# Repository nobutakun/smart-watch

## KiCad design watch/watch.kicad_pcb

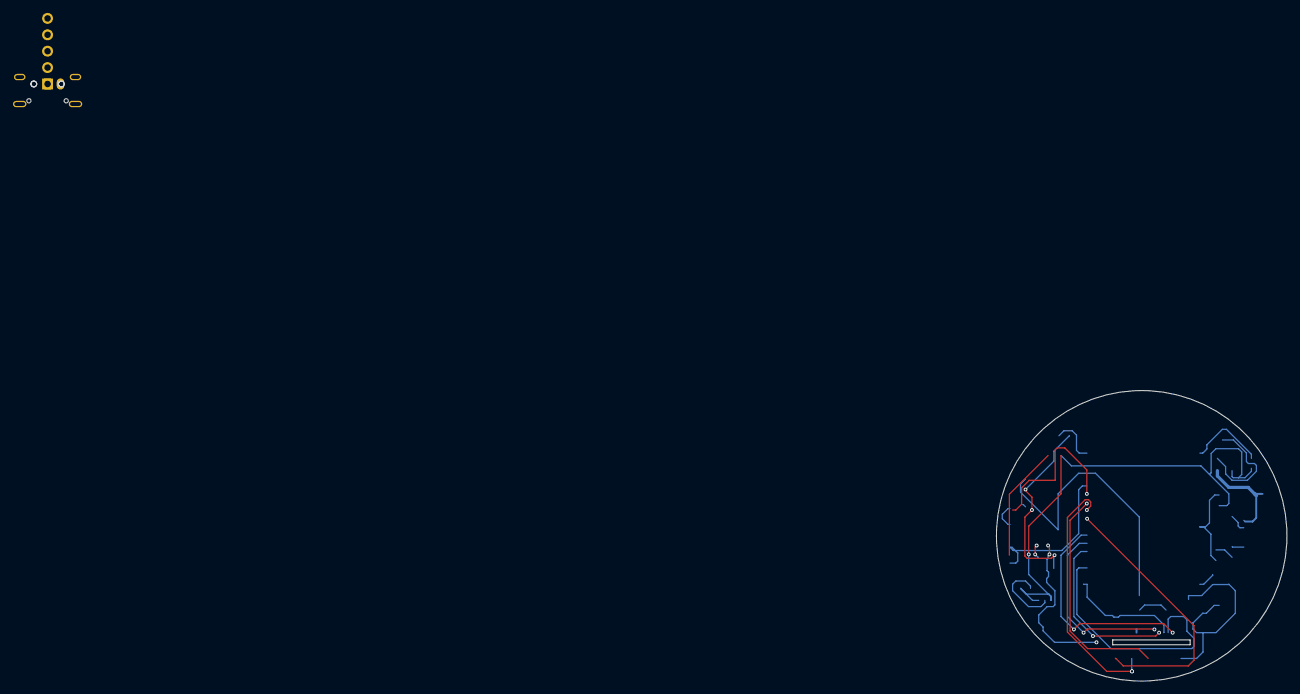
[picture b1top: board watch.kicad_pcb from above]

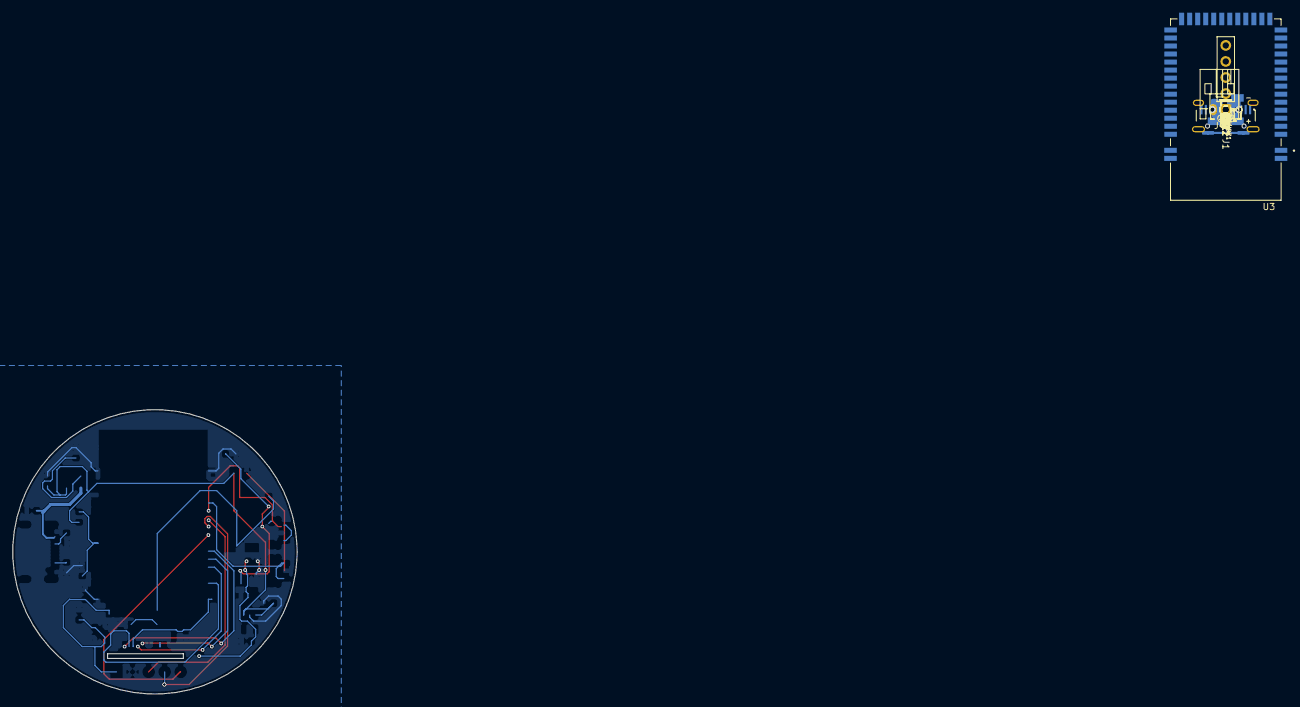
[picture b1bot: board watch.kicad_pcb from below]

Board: 2 copper layers, 45.0 x 45.0 mm, 31 parts (31 on the bottom side), 22 nets.

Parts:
BZ1: Buzzer; XDCR_CMT-0502-03-SMT-TR
C1, C2, C6, C10: 4.7uF; C_0603_1608Metric
C3, C4: C; C_0603_1608Metric
C5: 100nF; C_0603_1608Metric
C7, C9: 100 nF; C_0603_1608Metric
C8: 4.7 µF; C_0603_1608Metric
J1: USB_C_Receptacle_USB2.0_16P; USB_C_Receptacle_GCT_USB4105-xx-A_16P_TopMnt_Horizontal
J2: Conn_01x05; PinHeader_1x05_P2.54mm_Vertical
J3: Conn_01x12; GC9A01_FPC_12P_P0.7mm
J4: Conn_01x02; JST_PH_S2B-PH-K_1x02_P2.00mm_Horizontal
Q1, Q2: 2N7002; SOT-23
R1, R2: 5.1k; R_0603_1608Metric
R3: 10k; R_0603_1608Metric
R4: 100Ω; R_0603_1608Metric
R5: 100kΩ; R_0603_1608Metric
R6, R7: 1MΩ; R_0603_1608Metric
R8: 100 Ω; R_0603_1608Metric
R9: 100 kΩ; R_0603_1608Metric
SW1: Button_UP; SW_Push_1P1T-MP_NO_Horizontal_Alps_SKRTLAE010
SW2: Button_SELECT; SW_Push_1P1T-MP_NO_Horizontal_Alps_SKRTLAE010
U1: MCP73831-2-OT; SOT-23-5
U2: AP2112K-3.3; SOT-23-5
U3: E73-2G4M04S-52832; XCVR_E73-2G4M04S1B

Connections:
+3.3V: C4.1, C5.1, C6.1, C7.1, C8.1, C9.2, C10.2, J2.1, J3.3, J3.4, U2.5 (VOUT), U3.16 (VCC)
/BAT+: C2.2, C3.1, J4.1, R6.1, U1.3 (V_{BAT}), U2.1 (VIN), U2.3 (EN)
/BAT_SENSE: R6.2, R7.1, U3.8 (AIN4/P0.28)
/BUZZ_PWM: R8.1, U3.22 (P0.07)
/LCD_CS: J3.8, U3.32 (P0.17)
/LCD_DC: J3.7, U3.33 (SWO/P0.18)
/LCD_MOSI: J3.10, U3.30 (P0.15)
/LCD_RST: J3.11, U3.34 (P0.19)
/LCD_SCK: J3.9, U3.28 (P0.13)
/LEDK: J3.2, Q1.3 (D)
/P0.22: SW1.1, U3.39 (P0.22)
/P0.23: SW2.1, U3.40 (P0.23)
/RESET: J2.5, U3.36 (P0.21/~RESET)
/SWDCLK: J2.4, U3.37 (SWDCLK)
/SWDIO: J2.3, U3.38 (SWDIO)
GND: C1.1, C2.1, C3.2, C4.2, C5.2, C6.2, C7.2, C8.2, C9.1, C10.1, J1.A1 (GND), J1.A12 (GND), J1.B1 (GND), J1.B12 (GND), J2.2, J3.1, J3.5, J3.6, J3.12, J4.2, Q1.2 (S), Q2.2 (S), R1.2, R2.2, R3.2, R5.1, R7.2, R9.2, SW1.2, SW2.2, U1.2 (V_{SS}), U2.2 (GND), U3.0 (GND), U3.1 (GND), U3.2 (GND), U3.15 (GND), U3.42 (GND), U3.43 (GND)
unnamed: J1.A5 (CC1), R1.1
unnamed: J1.B5 (CC2), R2.1
unnamed: Q1.1 (G), R4.2, R5.2
unnamed: Q2.1 (G), R8.2, R9.1
unnamed: R3.1, U1.5 (PROG)
VBUS: C1.2, J1.A4 (VBUS), J1.A9 (VBUS), J1.B4 (VBUS), J1.B9 (VBUS), U1.4 (V_{DD})
